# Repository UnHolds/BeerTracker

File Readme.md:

# Beer Tracker

This repository contains the PCB, Enclosure and Code for the Beer Tracker.

The Beer Tracker allows a group of people to keep track of
various things (mainly beer).

## What does it do?

Each person gets a tracker. If a person logs a drink then the
total amount will be synced between all peers (if in reach).
If a peer is out of reach, it will be synced later. (It can
also sync via multiple hops: eg A syncs data to B and B syncs
As data to C).

The device also allows the user to see the current counts of
the other peers.

## Why?

This is a really good question...

It all started during a music festival, where we tracked our
beer consumption with a tally sheet. This worked great, as
long as we all are together in a group. But some people have
different music taste and hence the group was split and the
tracking failed. This major problem needed to be addressed. A
smart way to solve it would be to just you a tracking app, or
to write our own app if we are really fancy. But those
solutions aren't enough overengineered!!!. Hence we created
this project.

## Structure

- `code` - source code for the ESP32
- `enclosure` - STL files and FreeCAD files of the case
- `kicad` - schematic + pcb layout

## Images

TODO

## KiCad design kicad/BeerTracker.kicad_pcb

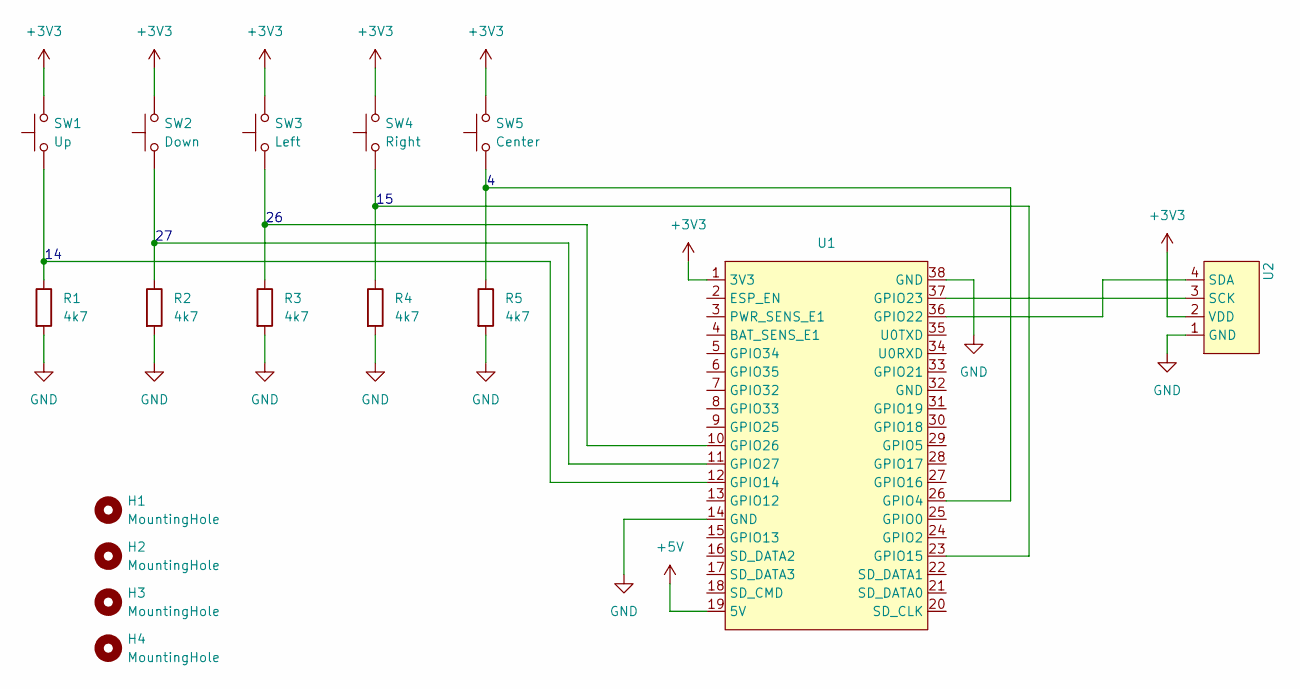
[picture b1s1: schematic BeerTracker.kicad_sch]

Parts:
H1, H2, H3, H4: MountingHole; MountingHole_3.2mm_M3
R1, R2, R3, R4, R5: 4k7; R_0805_2012Metric_Pad1.20x1.40mm_HandSolder
SW1: Up; SW_PUSH_6mm
SW2: Down; SW_PUSH_6mm
SW3: Left; SW_PUSH_6mm
SW4: Right; SW_PUSH_6mm
SW5: Center; SW_PUSH_6mm
U1: ESP32-DevKit-LiPo
U2: OLED

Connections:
+3V3: SW1.2, SW2.2, SW3.2, SW4.2, SW5.2, U1.1 (3V3), U2.2 (VDD)
+5V: U1.19 (5V)
GND: R1.2, R2.2, R3.2, R4.2, R5.2, U1.14 (GND), U1.38 (GND), U2.1 (GND)
unnamed: R5.1, SW5.1, U1.26 (GPIO4)
unnamed: R1.1, SW1.1, U1.12 (GPIO14)
unnamed: R4.1, SW4.1, U1.23 (GPIO15)
unnamed: U1.36 (GPIO22), U2.4 (SDA)
unnamed: U1.37 (GPIO23), U2.3 (SCK)
unnamed: R3.1, SW3.1, U1.10 (GPIO26)
unnamed: R2.1, SW2.1, U1.11 (GPIO27)

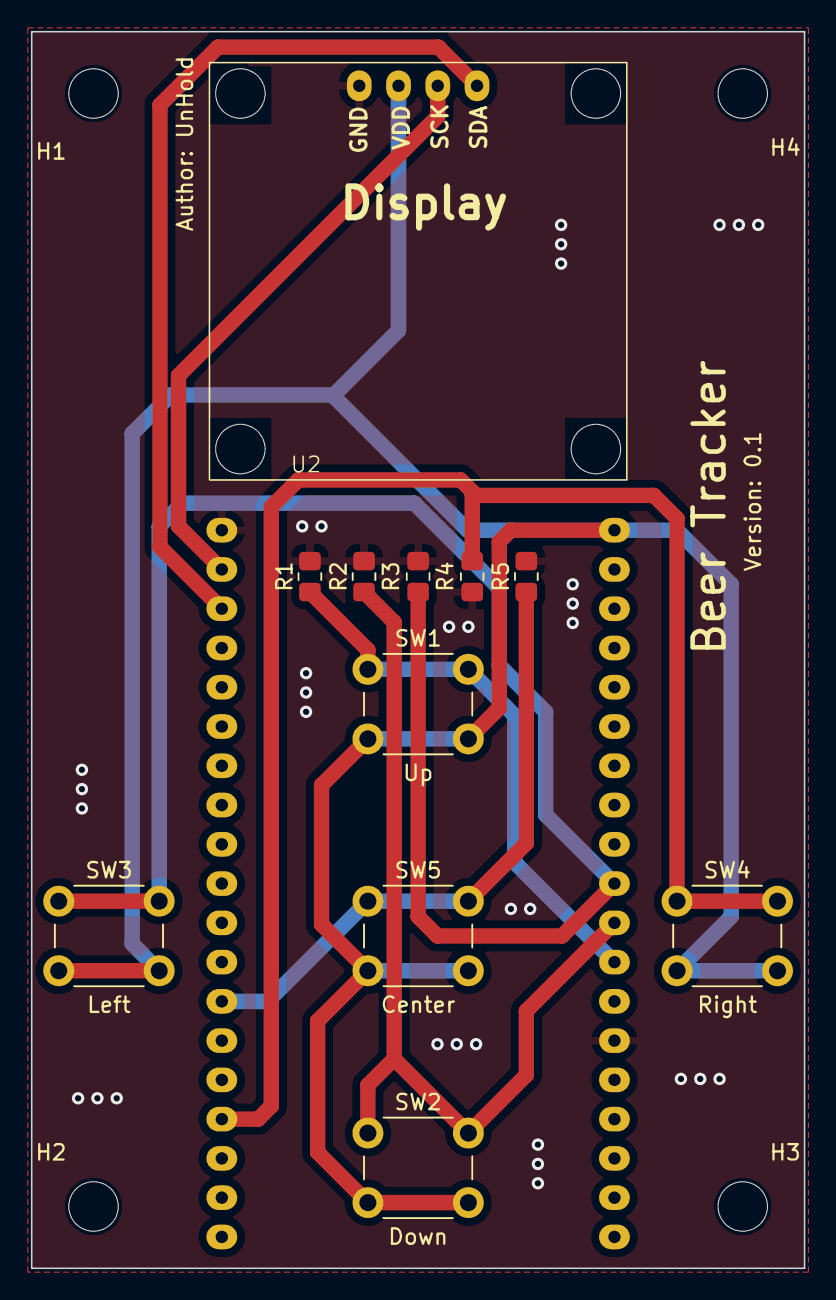
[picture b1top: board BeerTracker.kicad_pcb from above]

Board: 2 copper layers, 50.0 x 80.0 mm, 16 parts (1 on the bottom side), 9 nets.

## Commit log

2025-06-03 init code
2025-06-04 added simple display object
2025-06-04 added input handler
2025-06-04 fixed button read
2025-06-04 added espnow + simplefs
2025-06-04 added better menu
2025-06-04 reenable sleep
2025-06-05 added v0.1 pcb
2025-06-05 moved last_command init
2025-06-29 added time support + user view + bug fixes
2025-06-29 added better rst + staggered send
2025-06-29 fixed sleep time + sleep screen + time zone
2025-06-29 added basic enclousure
2025-06-29 added top and spacer
2025-08-03 added missing users
2025-08-03 removed old case
2025-08-03 added V2 case of the beer tracker
2025-08-03 added stl exports
2025-08-03 rename
2025-08-03 added readme
2025-08-03 more readme
2025-08-03 changed sec to send
2025-08-04 added better button support + added lock screen
2025-08-04 added peers
2025-08-04 added better error msg
2025-08-04 fixed sending to peers
2025-08-06 added icons
2025-08-06 added more icons
2025-08-06 added more icons + leaderboard
2025-08-06 added crown and easter egg
2025-08-06 added thomas
2025-08-11 simple fixed for 2.0 release
2025-08-11 added ignore for lockscreen if wakeup timer
